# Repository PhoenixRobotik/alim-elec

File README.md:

# alim-elec
La carte Alimentation, design électronique.

* LD1084, adjustable : 
  * R1=120
  * VRef = 1.25V
  * Vo = VRef × (1 + R2/R1)
  * R2 = R1 × (Vo / VRef - 1) 
  * Vo = 9V => R2 = 744 ~ 750 ohm

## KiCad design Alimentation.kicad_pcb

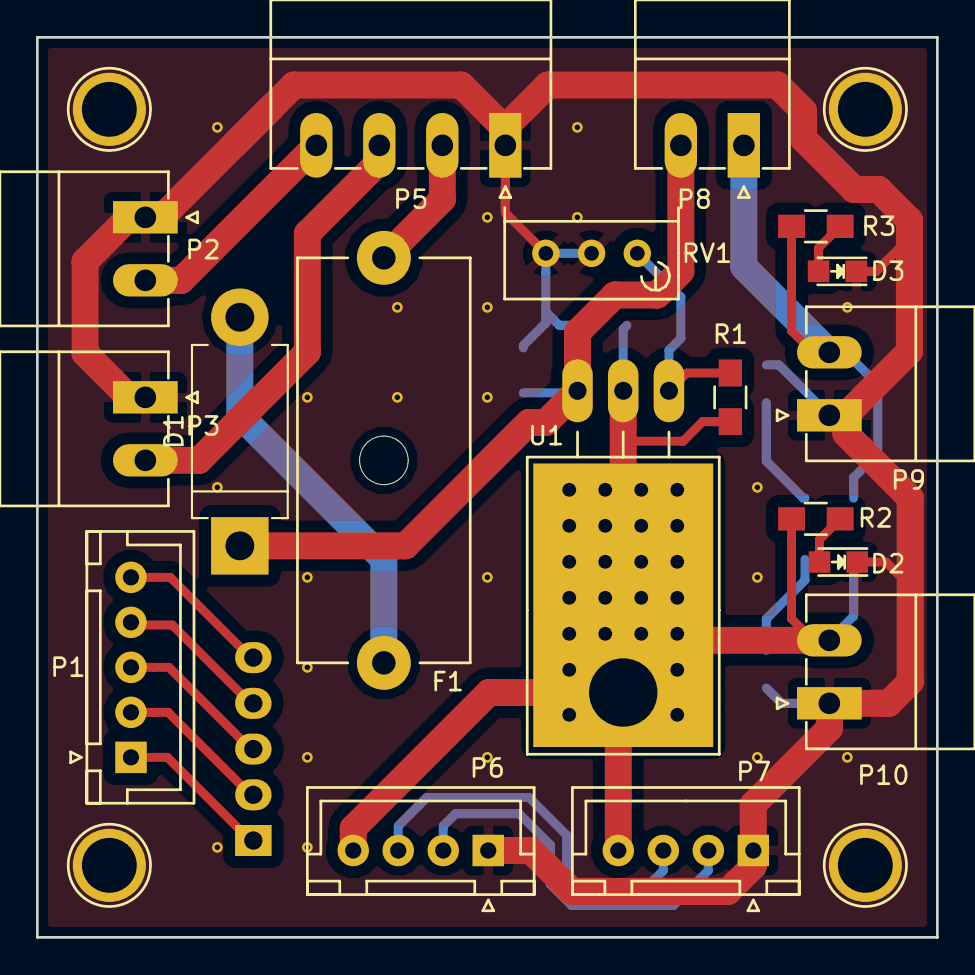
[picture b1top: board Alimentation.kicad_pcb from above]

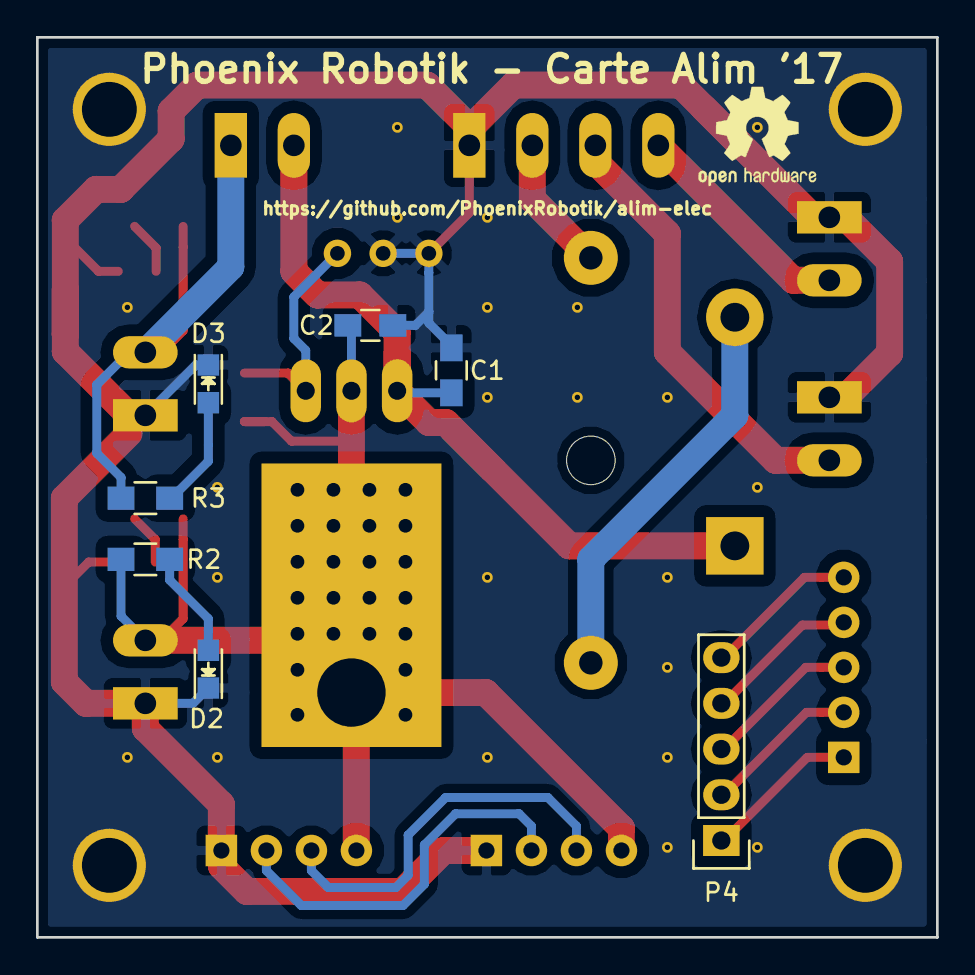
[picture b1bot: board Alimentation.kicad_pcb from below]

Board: 2 copper layers, 50.0 x 50.0 mm, 25 parts (7 on the bottom side), 18 nets.

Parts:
C1, C2: 10µ; C_0805_HandSoldering
D1: DiodeProtection; D_DO-201AD_P12.70mm_Horizontal
D2, D2#2, D3, D3#2: LED; LED_0805
F1: Fuse; Fuseholder5x20_horiz_open_Schurter_0031_8201
P1: Prise_Equilibrage; JST_XH_B05B-XH-A_05x2.50mm_Straight
P2: Prise_Alim; PhoenixContact_MC-G_02x3.50mm_Angled
P3: Prise_Batterie; PhoenixContact_MC-G_02x3.50mm_Angled
P4: ConnecteurBippeur; Pin_Header_Straight_1x05
P5: CONN_01X04; PhoenixContact_MC-G_04x3.50mm_Angled
P6, P7: CAN_conn; JST_XH_B04B-XH-A_04x2.50mm_Straight
P8, P9, P10: CONN_01X02; PhoenixContact_MC-G_02x3.50mm_Angled
R1: 120; R_0805_HandSoldering
R2, R2#2, R3, R3#2: R; R_0805_HandSoldering
RV1: POT; Potentiometer_Bourns_3296W_3-8Zoll_Inline_ScrewUp
U1: LD1084V; TO-220_Neutral123_Horizontal_LargePads

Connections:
+9V: C2.1, P6.4, P7.4, P10.2, R1.1, R2.1, R2#2.1, U1.2
CAN_H: P6.2, P7.2
CAN_L: P6.3, P7.3
GND: C1.2, C2.2, D2.1, D2#2.1, D3.1, D3#2.1, P2.1, P3.1, P5.1, P6.1, P7.1, P9.1, P10.1, RV1.2, RV1.3
unnamed: C1.1, D1.1, P8.2, U1.3
unnamed: D1.2, F1.1
unnamed: D2.2, D2#2.2, R2.2, R2#2.2
unnamed: D3.2, D3#2.2, R3.2, R3#2.2
unnamed: F1.2, P5.2
unnamed: P1.1, P4.1
unnamed: P1.2, P4.2
unnamed: P1.3, P4.3
unnamed: P1.4, P4.4
unnamed: P1.5, P4.5
unnamed: P2.2, P5.4
unnamed: P3.2, P5.3
unnamed: R1.2, RV1.1, U1.1
Non_régulé: P8.1, P9.2, R3.1, R3#2.1

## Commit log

2017-01-23 avancement carte alim
2017-02-02 fin du schéma ?
2017-02-03 association footprint + placement
2017-02-03 prise en compte des changements dans la lib perso
2017-02-03 inversion de deux pin sur le connecteur de switch
2017-02-03 routage préliminaire (dirty)
2017-02-06 met la masse à l'extérieur
2017-02-06 pin 1 des connecteurs sur la masse
2017-02-07 routage terminé ?
2017-02-10 ajoute les trous pour les vis
2017-02-10 remove useless references for screw holes
2017-02-10 déplace les deux connecteurs de sortie
2017-02-10 recentre le régul
2017-02-11 clean+fix cache libs + new lib path
2017-02-11 ajoute thermal pad régul + connection trous vis à la masse
2017-02-11 moved headers
2017-02-12 duplique les led sur l'autre face
2017-02-12 corrige les erreurs ERC
2017-02-12 modif empreinte régul avec plein de trous
2017-02-12 3d led
2017-02-12 retourné connecteur CAN
2017-02-13 ajoute des vias entre les deux plans de masse
2017-02-16 ajout nom, url et export gerber
2017-02-16 added global gerber
2017-02-16 new global gerbers
2017-02-16 removed unnecessary files (CrtYd, drl_map.gbr) and merged .drl files
2017-02-16 correct OSHW logo
2017-03-12 good schottky footprint
2017-03-12 fix last commit
2017-04-07 corrige sens diode D1
2017-05-23 ajoute des TODO
